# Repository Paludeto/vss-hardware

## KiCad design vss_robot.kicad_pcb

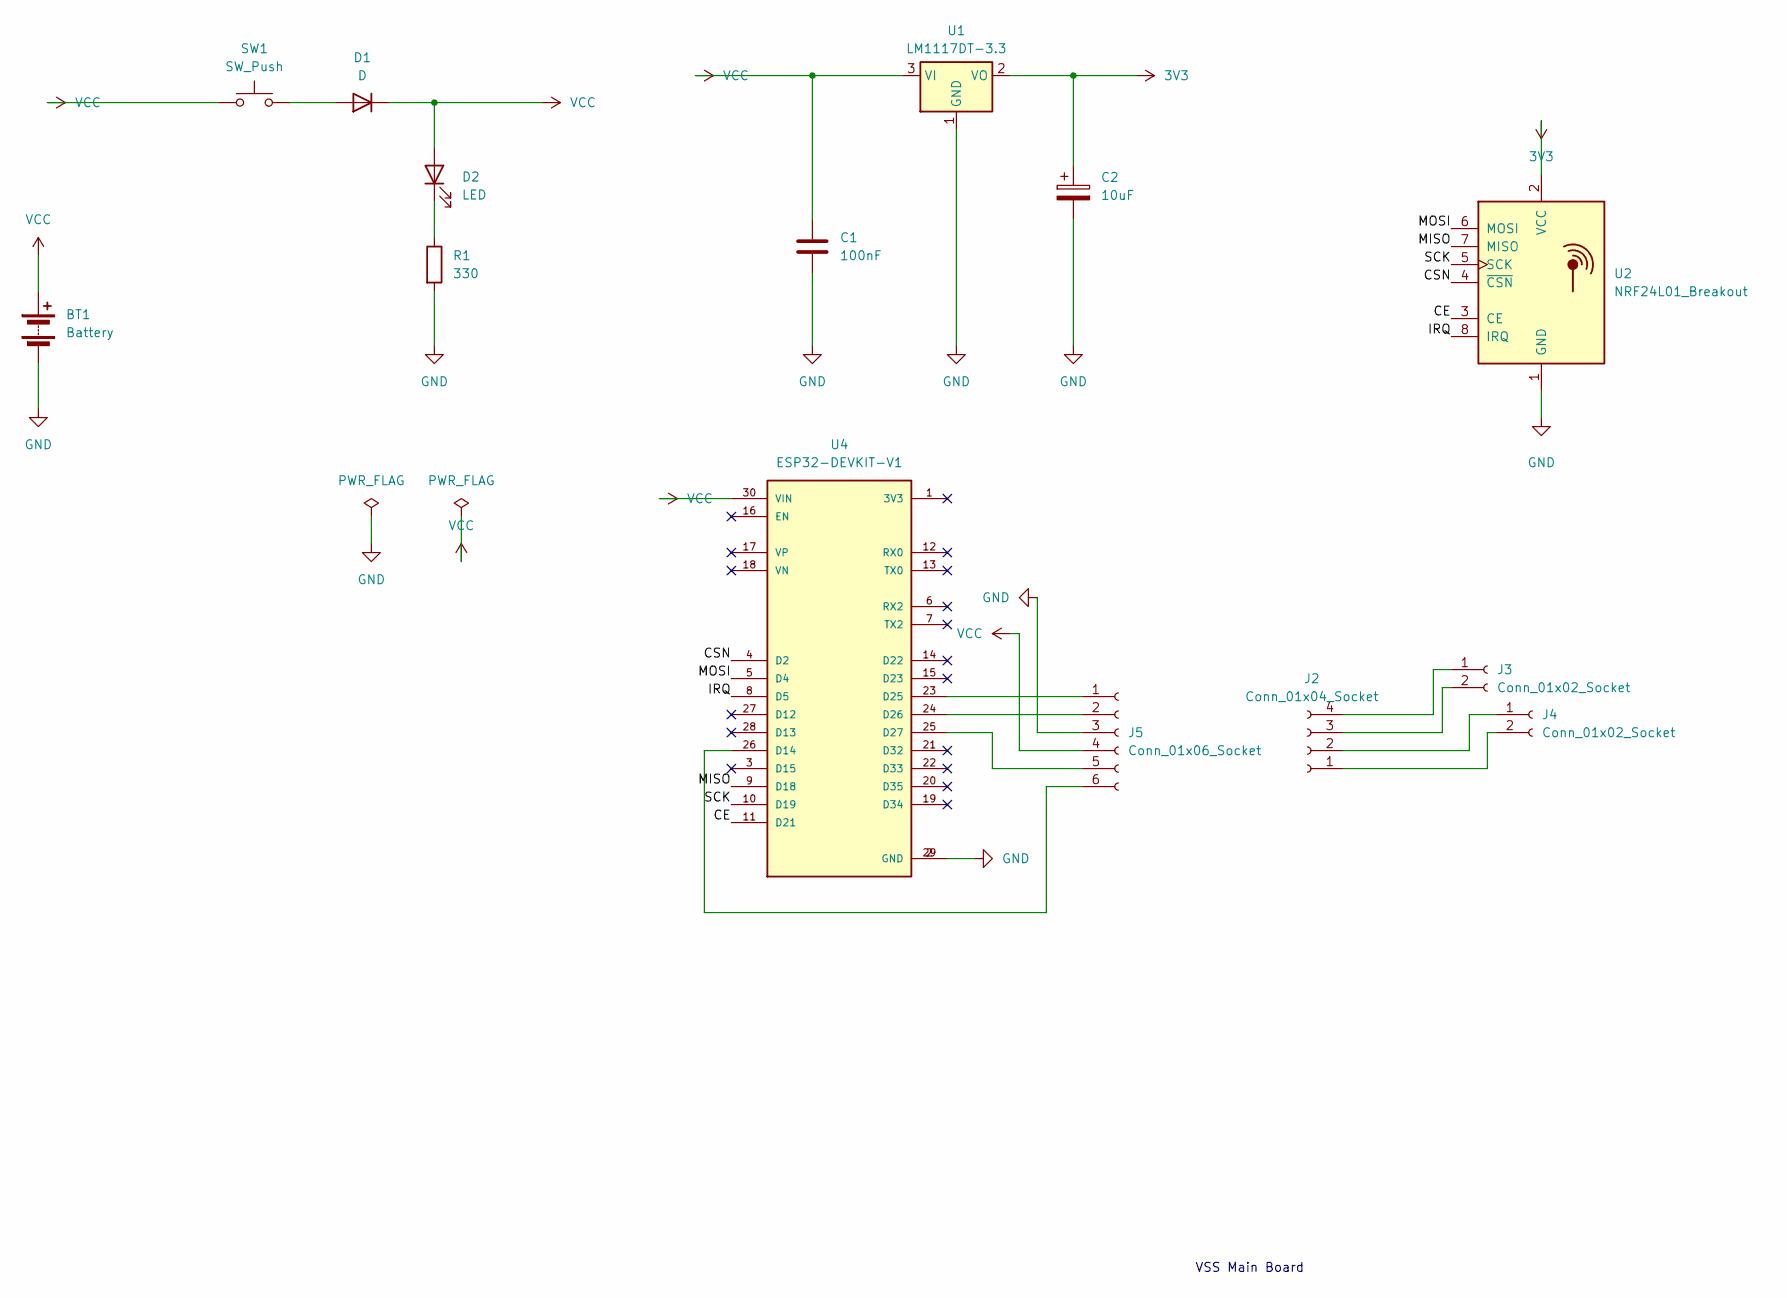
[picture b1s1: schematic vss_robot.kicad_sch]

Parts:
BT1: Battery; PinHeader_1x02_P2.54mm_Horizontal
C1: 100nF; CP_Radial_D5.0mm_P2.50mm
C2: 10uF; CP_Radial_D5.0mm_P2.50mm
D1: D; D_A-405_P5.08mm_Vertical_AnodeUp
D2: LED; LED_D5.0mm
J2: Conn_01x04_Socket; PinSocket_1x04_P2.54mm_Horizontal
J3, J4: Conn_01x02_Socket; PinSocket_1x02_P2.54mm_Horizontal
J5: Conn_01x06_Socket; PinSocket_1x06_P2.54mm_Horizontal
R1: 330; R_Axial_DIN0207_L6.3mm_D2.5mm_P7.62mm_Horizontal
SW1: SW_Push; SW_Slide-03_Wuerth-WS-SLTV_10x2.5x6.4_P2.54mm
U1: LM1117DT-3.3; TO-220-3_Horizontal_TabDown; MPN LM1117T-3.3
U2: NRF24L01_Breakout; nRF24L01_Breakout
U4: ESP32-DEVKIT-V1; MODULE_ESP32_DEVKIT_V1; PARTREV N/A

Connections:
3V3: C2.1, U1.2 (VO), U2.2 (VCC)
/CE: U2.3 (CE), U4.11 (D21)
/CSN: U2.4 (~CSN), U4.4 (D2)
/IRQ: U2.8 (IRQ), U4.8 (D5)
/MISO: U2.7 (MISO), U4.9 (D18)
/MOSI: U2.6 (MOSI), U4.5 (D4)
/SCK: U2.5 (SCK), U4.10 (D19)
GND: BT1.2 (-), C1.2, C2.2, J5.3, R1.2, U1.1 (GND), U2.1 (GND), U4.2 (GND), U4.29 (GND)
unnamed: D1.2 (A), SW1.2
unnamed: D2.1 (K), R1.1
unnamed: J2.1, J4.2
unnamed: J2.2, J4.1
unnamed: J2.3, J3.2
unnamed: J2.4, J3.1
unnamed: J5.1, U4.23 (D25)
unnamed: J5.2, U4.24 (D26)
unnamed: J5.5, U4.25 (D27)
unnamed: J5.6, U4.26 (D14)
VCC: BT1.1 (+), C1.1, D1.1 (K), D2.2 (A), J5.4, SW1.1, U1.3 (VI), U4.30 (VIN)

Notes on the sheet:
VSS Main Board

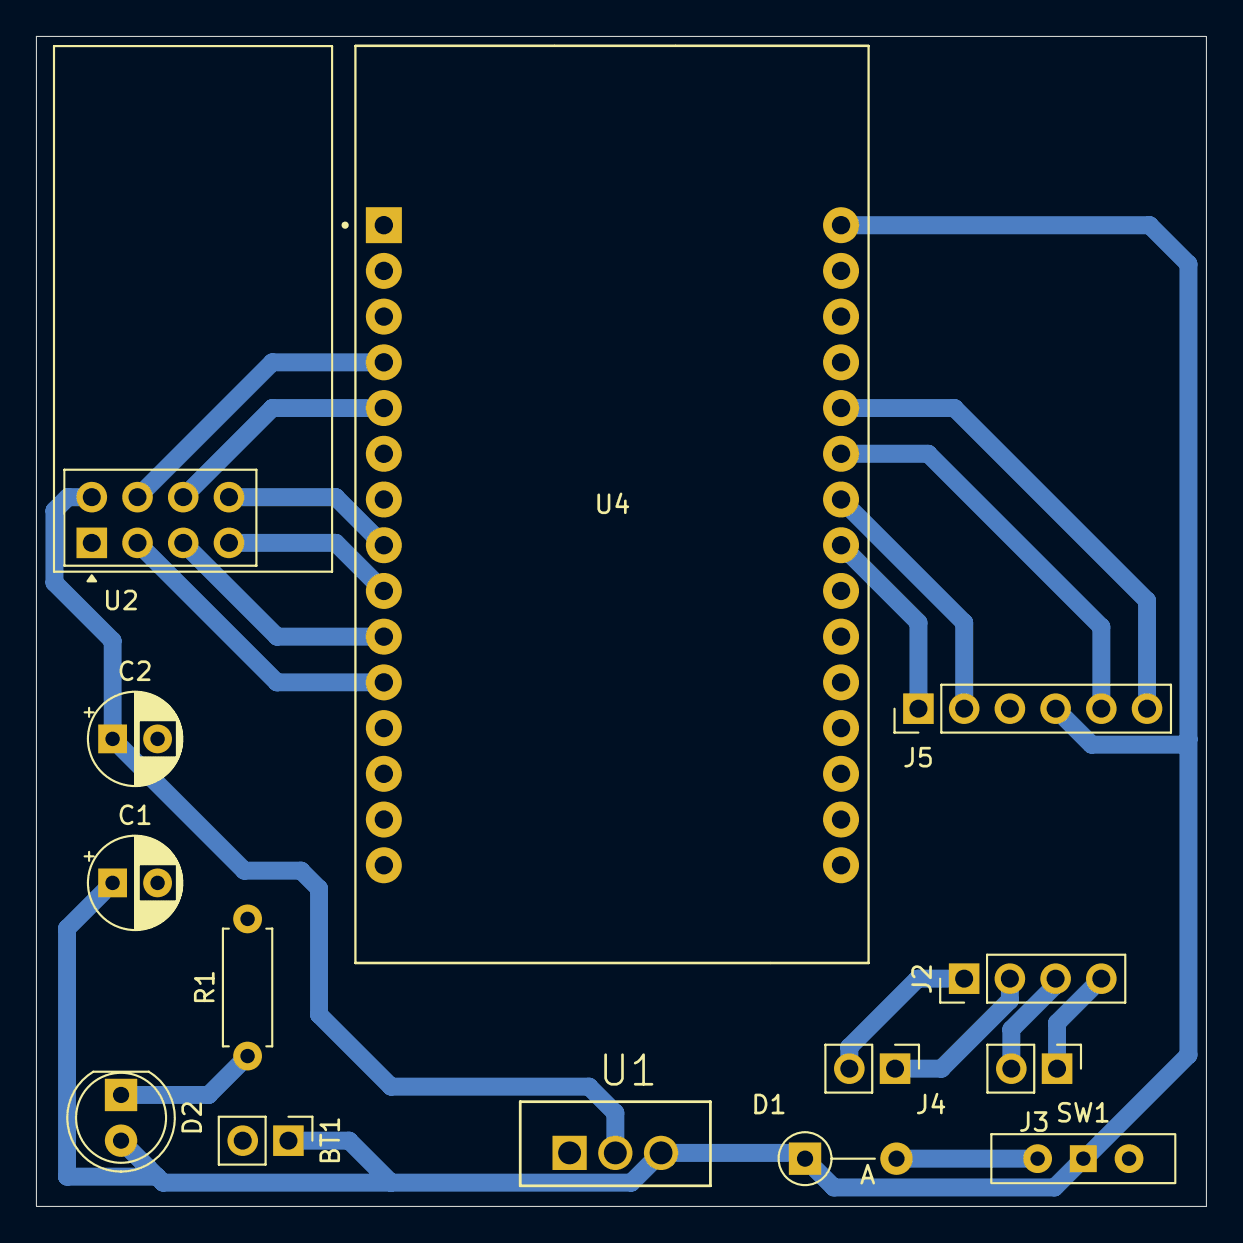
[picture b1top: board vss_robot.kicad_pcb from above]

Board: 2 copper layers, 65.0 x 65.0 mm, 14 parts (0 on the bottom side), 19 nets.

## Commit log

2024-10-07 add files
2024-10-07 grossura da trilha, layer e posicionamento
